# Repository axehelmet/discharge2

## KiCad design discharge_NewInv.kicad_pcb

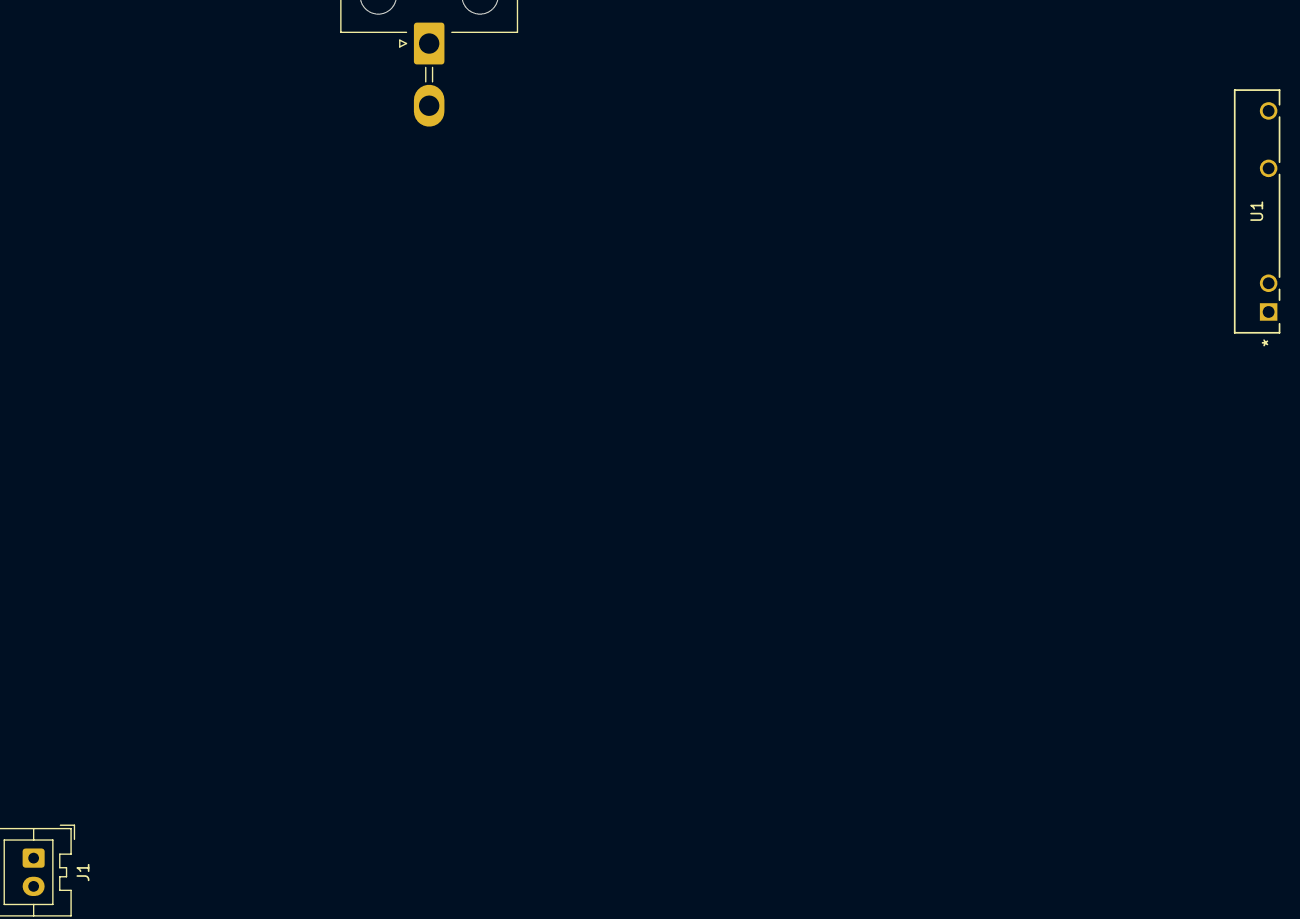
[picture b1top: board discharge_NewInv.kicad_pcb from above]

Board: 2 copper layers, 3 parts (0 on the bottom side), 4 nets, no tracks yet.

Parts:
J1: Conn_01x02; JST_XA_B02B-XASK-1_1x02_P2.50mm_Vertical
J2: Conn_01x02; Molex_Mini-Fit_Jr_5569-02A1_2x01_P4.20mm_Horizontal
U1: AQZ404; PAN_AQZ404-SIP4_PAN

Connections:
unnamed: J1.1, U1.2
unnamed: J1.2, U1.1
unnamed: J2.1, U1.4
unnamed: J2.2, U1.3

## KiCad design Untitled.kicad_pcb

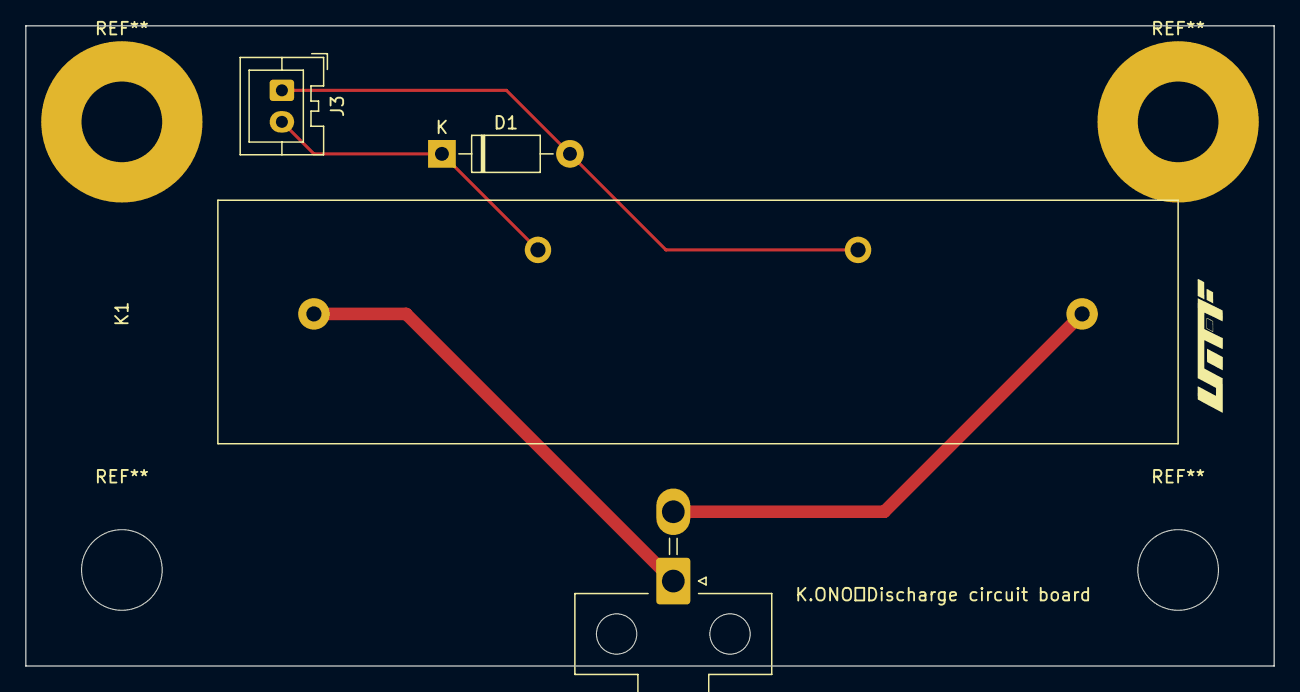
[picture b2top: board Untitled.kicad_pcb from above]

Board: 2 copper layers, 99.1 x 50.8 mm, 4 parts (0 on the bottom side), 4 nets.

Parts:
D1: 1N4004; D_DO-41_SOD81_P10.16mm_Horizontal
J1: Conn_01x02; Molex_Mini-Fit_Jr_5569-02A1_2x01_P4.20mm_Horizontal
J3: Conn_01x02; JST_XA_B02B-XASK-1_1x02_P2.50mm_Vertical
K1: 3350-4275-126; 3350-xxxx-126

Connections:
+12V: D1.1 (K), J3.2, K1.2
GND: D1.2 (A), J3.1, K1.3
unnamed: J1.1, K1.4
unnamed: J1.2, K1.1

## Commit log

2023-11-28 board complete
2023-11-28 connectors are changed
2023-11-28 add data
2023-12-08 AddNewCircuits
